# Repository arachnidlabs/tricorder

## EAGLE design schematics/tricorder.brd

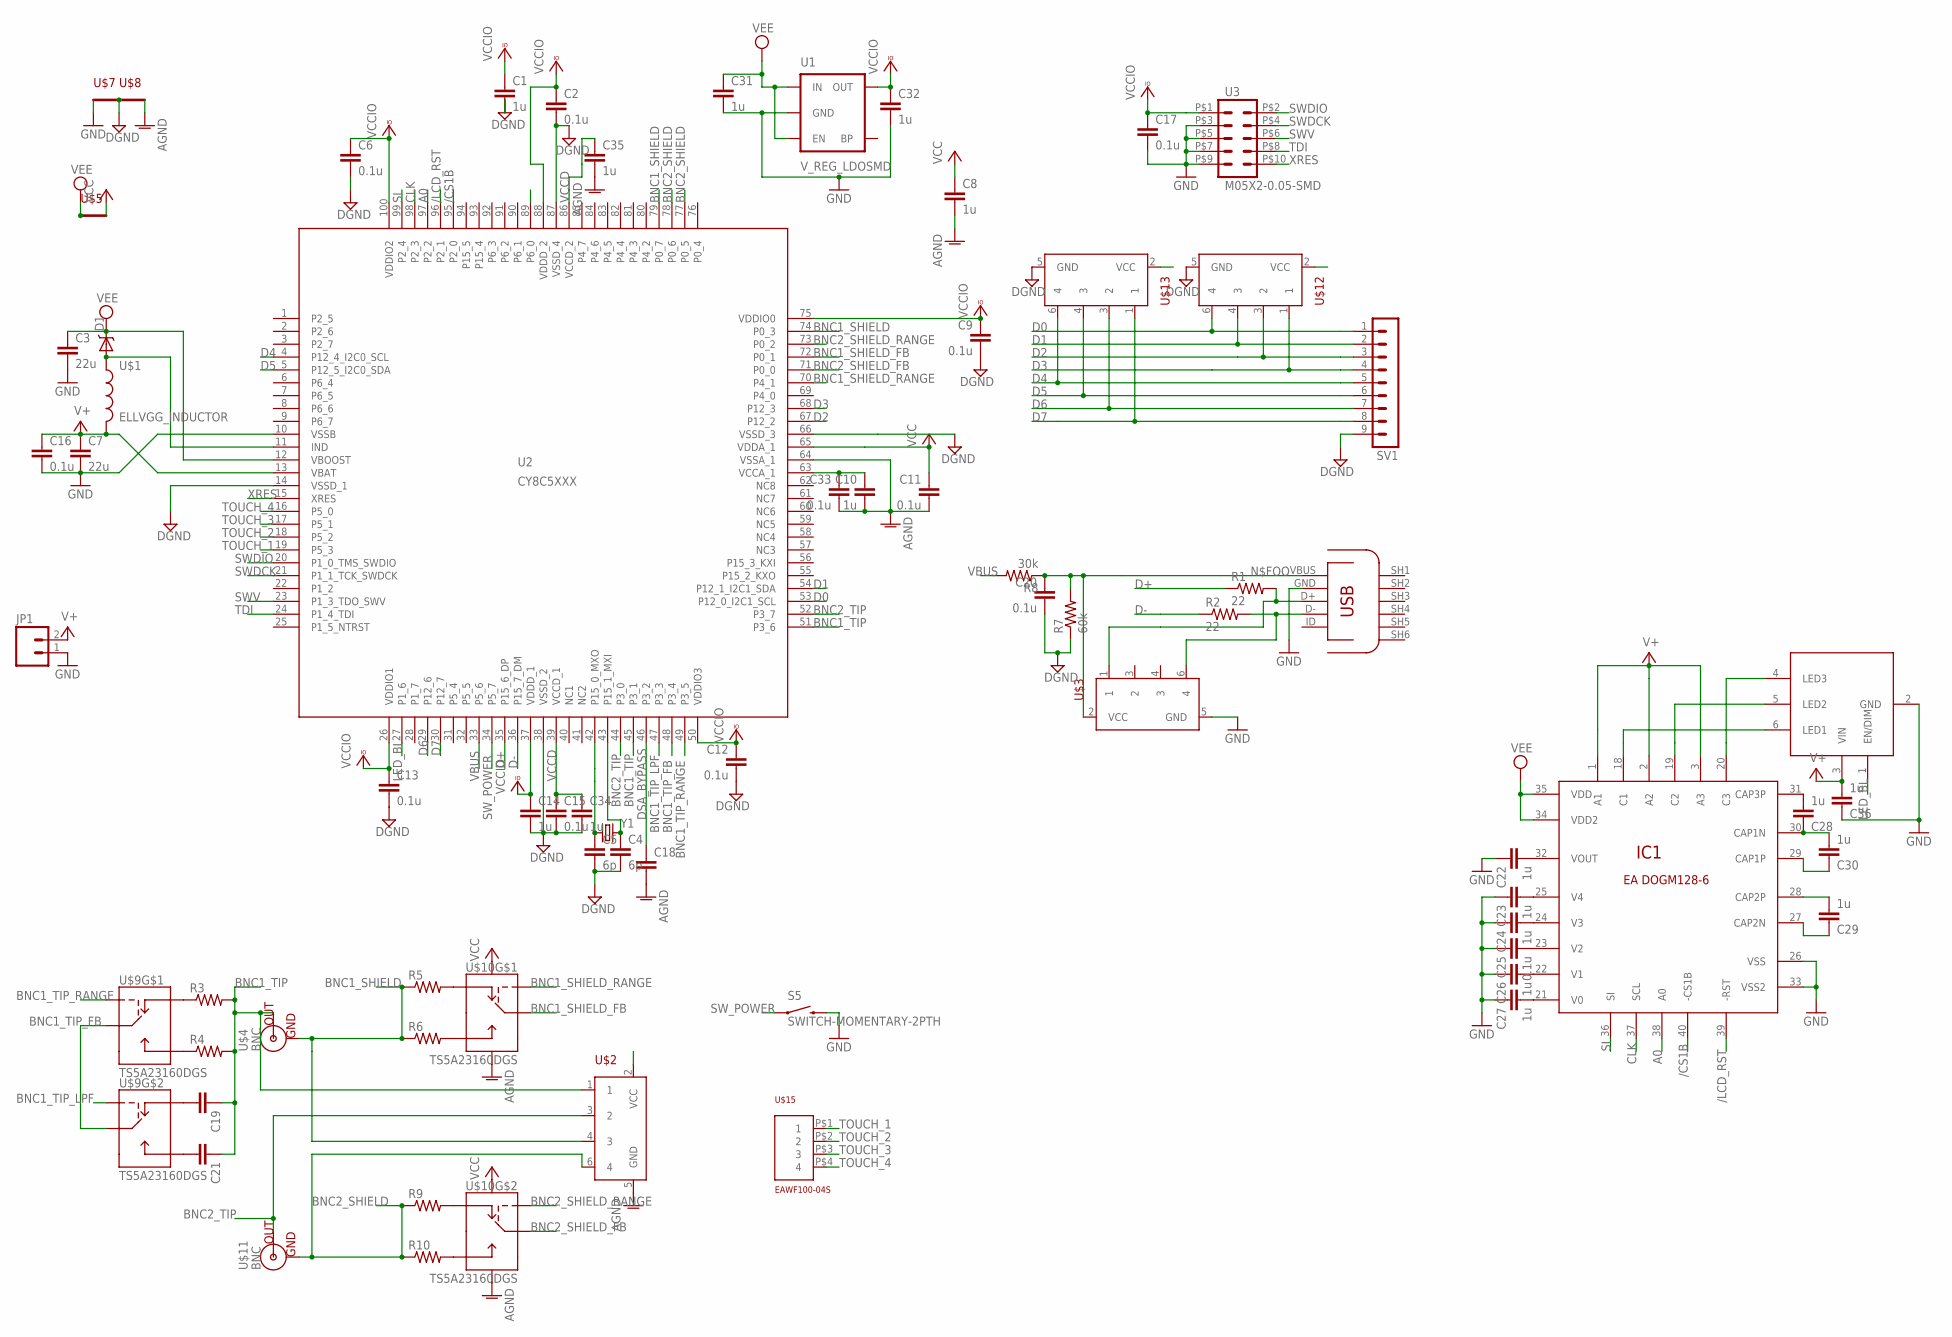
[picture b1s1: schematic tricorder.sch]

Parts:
C1, C8, C10, C14, C31, C32, C34, C35: 1u; 0603-CAP
C2, C9, C11, C15, C16, C20, C33: 0.1u; 0603-CAP
C3, C7: 22u; 0805
C4, C5: 6p; 0603-CAP
C6, C12, C13, C17, C25: 0.1u; C0603K
C18: CAP0805; 0805
C19, C21: CAP0603-CAP; 0603-CAP
C22, C23, C24, C26, C27, C28, C29, C30, C36: 1u; C0603K
D1: DIODE-SCHOTTKY_; SMA-DIODE
IC1: EADOGM128
JP1: M02PTH; 1X02
R1, R2: 22; 0603-RES
R3, R4, R5, R6, R9, R10: RESISTOR0603-RES; 0603-RES
R7: 60k; 0603-RES
R8: 30k; 0603-RES
S5: SWITCH-MOMENTARY-2PTH; TACTILE-PTH
SV1: MA09-1W
U1: V_REG_LDOSMD; SOT23-5
U2: CY8C5XXX; TQFP-14X14-100
U3: M05X2-0.05-SMD; PINHD-2X5-0.05-SMD
U7: MICROUSB; USB-MICROB
U$1: ELLVGG_INDUCTOR
U$2, U$3, U$12, U$13: ESD5V3U4RRSSOT363; SOT363_INFINEON
U$4, U$11: BNC; BNC_RA
U$5, U$7, U$8: SHORT-2
U$9, U$10: TS5A23160DGS; MSOP10
U$15: EAWF100-04S
U$16: CAT4003B; SOT23-6
Y1: XRCGB_XTAL; XRCGB-XTAL

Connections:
/CS1B: IC1.40 (-CS1B), U2.95 (P2_0)
/LCD_RST: IC1.39 (-RST), U2.96 (P2_1)
A0: IC1.38 (A0), U2.97 (P2_2)
AGND: C8.2, C10.2, C11.2, C18.2, C33.2, C35.2, U2.64 (VSSA_1), U$2.5 (GND), U$8.P$2, U$9.3 (GND), U$10.3 (GND)
BNC1_SHIELD: R5.1, R6.1, U2.74 (P0_3), U2.79 (P0_7), U$2.4 (3), U$4.SHIELD_1 (GND), U$4.SHIELD_2 (GND)
BNC1_SHIELD_FB: U2.72 (P0_1), U$10.10 (COM)
BNC1_SHIELD_RANGE: U2.70 (P4_1), U$10.1 (IN)
BNC1_TIP: C19.1, C21.1, R3.2, R4.2, U2.45 (P3_1), U2.51 (P3_6), U$2.1, U$4.TIP (OUT)
BNC1_TIP_FB: U2.48 (P3_4), U$9.6 (COM), U$9.10 (COM)
BNC1_TIP_LPF: U2.47 (P3_3), U$9.5 (IN)
BNC1_TIP_RANGE: U2.49 (P3_5), U$9.1 (IN)
BNC2_SHIELD: R9.1, R10.1, U2.77 (P0_5), U2.78 (P0_6), U$2.6 (4), U$11.SHIELD_1 (GND), U$11.SHIELD_2 (GND)
BNC2_SHIELD_FB: U2.71 (P0_0), U$10.6 (COM)
BNC2_SHIELD_RANGE: U2.73 (P0_2), U$10.5 (IN)
BNC2_TIP: U2.44 (P3_0), U2.52 (P3_7), U$2.3 (2), U$11.TIP (OUT)
CLK: IC1.37 (SCL), U2.98 (P2_3)
CLKI: C4.1, U2.43 (P15_1_MXI), Y1.2
CLKO: C5.1, U2.42 (P15_0_MXO), Y1.1
D0: SV1.1, U2.53 (P12_0_I2C1_SCL), U$12.6 (4)
D1: SV1.2, U2.54 (P12_1_I2C1_SDA), U$12.4 (3)
D2: SV1.3, U2.67 (P12_2), U$12.3 (2)
D3: SV1.4, U2.68 (P12_3), U$12.1
D4: SV1.5, U2.4 (P12_4_I2C0_SCL), U$13.6 (4)
D5: SV1.6, U2.5 (P12_5_I2C0_SDA), U$13.4 (3)
D6: SV1.7, U2.29 (P12_6), U$13.3 (2)
D7: SV1.8, U2.30 (P12_7), U$13.1
D+: R1.1, U2.35 (P15_6_DP)
D+IN: R1.2, U7.D+, U$3.1
D-: R2.1, U2.36 (P15_7_DM)
D-IN: R2.2, U7.D-, U$3.6 (4)
DGND: C1.2, C2.2, C4.2, C5.2, C6.2, C9.2, C12.2, C13.2, C14.2, C15.2, C20.2, C34.2, R7.1, SV1.9, U2.14 (VSSD_1), U2.38 (VSSD_2), U2.66 (VSSD_3), U2.87 (VSSD_4), U$7.P$2, U$8.P$1, U$12.5 (GND), U$13.5 (GND)
DSA_BYPASS: C18.1, U2.46 (P3_2)
GND: C3.2, C7.2, C16.2, C17.2, C22.1, C23.1, C24.1, C25.1, C26.1, C27.1, C31.2, C32.2, C36.1, IC1.26 (VSS), IC1.33 (VSS2), JP1.1, S5.3 (2), U1.2 (GND), U2.10 (VSSB), U3.P$3 (3), U3.P$5 (5), U3.P$7 (7), U3.P$9 (9), U7.GND, U$3.5 (GND), U$7.P$1, U$16.2 (GND)
LED_BL: U2.27 (P1_6), U$16.1 (EN/DIM)
unnamed: R3.1, U$9.9 (NC)
unnamed: R4.1, U$9.2 (NO)
unnamed: C10.1, C33.1, U2.63 (VCCA_1)
unnamed: R5.2, U$10.9 (NC)
unnamed: R6.2, U$10.2 (NO)
unnamed: C19.2, U$9.7 (NC)
unnamed: C21.2, U$9.4 (NO)
unnamed: R9.2, U$10.7 (NC)
unnamed: R10.2, U$10.4 (NO)
unnamed: C22.2, IC1.32 (VOUT)
unnamed: C23.2, IC1.25 (V4)
unnamed: C24.2, IC1.24 (V3)
unnamed: C25.2, IC1.23 (V2)
unnamed: C26.2, IC1.22 (V1)
unnamed: C27.2, IC1.21 (V0)
unnamed: C28.1, C30.2, IC1.30 (CAP1N)
unnamed: C28.2, IC1.31 (CAP3P)
unnamed: C30.1, IC1.29 (CAP1P)
unnamed: C29.2, IC1.28 (CAP2P)
unnamed: C29.1, IC1.27 (CAP2N)
unnamed: IC1.18 (C1), U$16.6 (LED1)
unnamed: IC1.19 (C2), U$16.5 (LED2)
unnamed: IC1.20 (C3), U$16.4 (LED3)
unnamed: D1.A, U2.11 (IND), U$1.P$1 (1)
N$FOO: C20.1, R7.2, R8.1, U7.VBUS (VCC), U$3.2 (VCC)
NC1: U$13.2 (VCC)
NC2: U$12.2 (VCC)
NC3: U$2.2 (VCC)
SI: IC1.36 (SI), U2.99 (P2_4)
SWDCK: U2.21 (P1_1_TCK_SWDCK), U3.P$4 (4)
SWDIO: U2.20 (P1_0_TMS_SWDIO), U3.P$2 (2)
SWV: U2.23 (P1_3_TDO_SWV), U3.P$6 (6)
SW_MENU: U2.89 (P6_0)
SW_POWER: S5.1, U2.34 (P5_7)
TDI: U2.24 (P1_4_TDI), U3.P$8 (8)
TOUCH_1: U2.19 (P5_3), U$15.P$1 (1)
TOUCH_2: U2.18 (P5_2), U$15.P$2 (2)
TOUCH_3: U2.17 (P5_1), U$15.P$3 (3)
TOUCH_4: U2.16 (P5_0), U$15.P$4 (4)
V+: C7.1, C16.1, C36.2, IC1.1 (A1), IC1.2 (A2), IC1.3 (A3), JP1.2, U2.13 (VBAT), U$1.P$2 (2), U$16.3 (VIN)
VBUS: R8.2, U2.33 (P5_6)
VCC: C8.1, C11.1, U2.65 (VDDA_1), U$5.P$2, U$9.8 (VCC), U$10.8 (VCC)
VCCD: C15.1, C34.1, C35.1, U2.39 (VCCD_1), U2.86 (VCCD_2)
VCCIO: C1.1, C2.1, C6.1, C9.1, C12.1, C13.1, C14.1, C17.1, C32.1, U1.5 (OUT), U2.26 (VDDIO1), U2.37 (VDDD_1), U2.50 (VDDIO3), U2.75 (VDDIO0), U2.88 (VDDD_2), U2.100 (VDDIO2), U3.P$1 (1)
VEE: C3.1, C31.1, D1.C, IC1.34 (VDD2), IC1.35 (VDD), U1.1 (IN), U1.3 (EN), U2.12 (VBOOST), U$5.P$1
XRES: U2.15 (XRES), U3.P$10 (10)

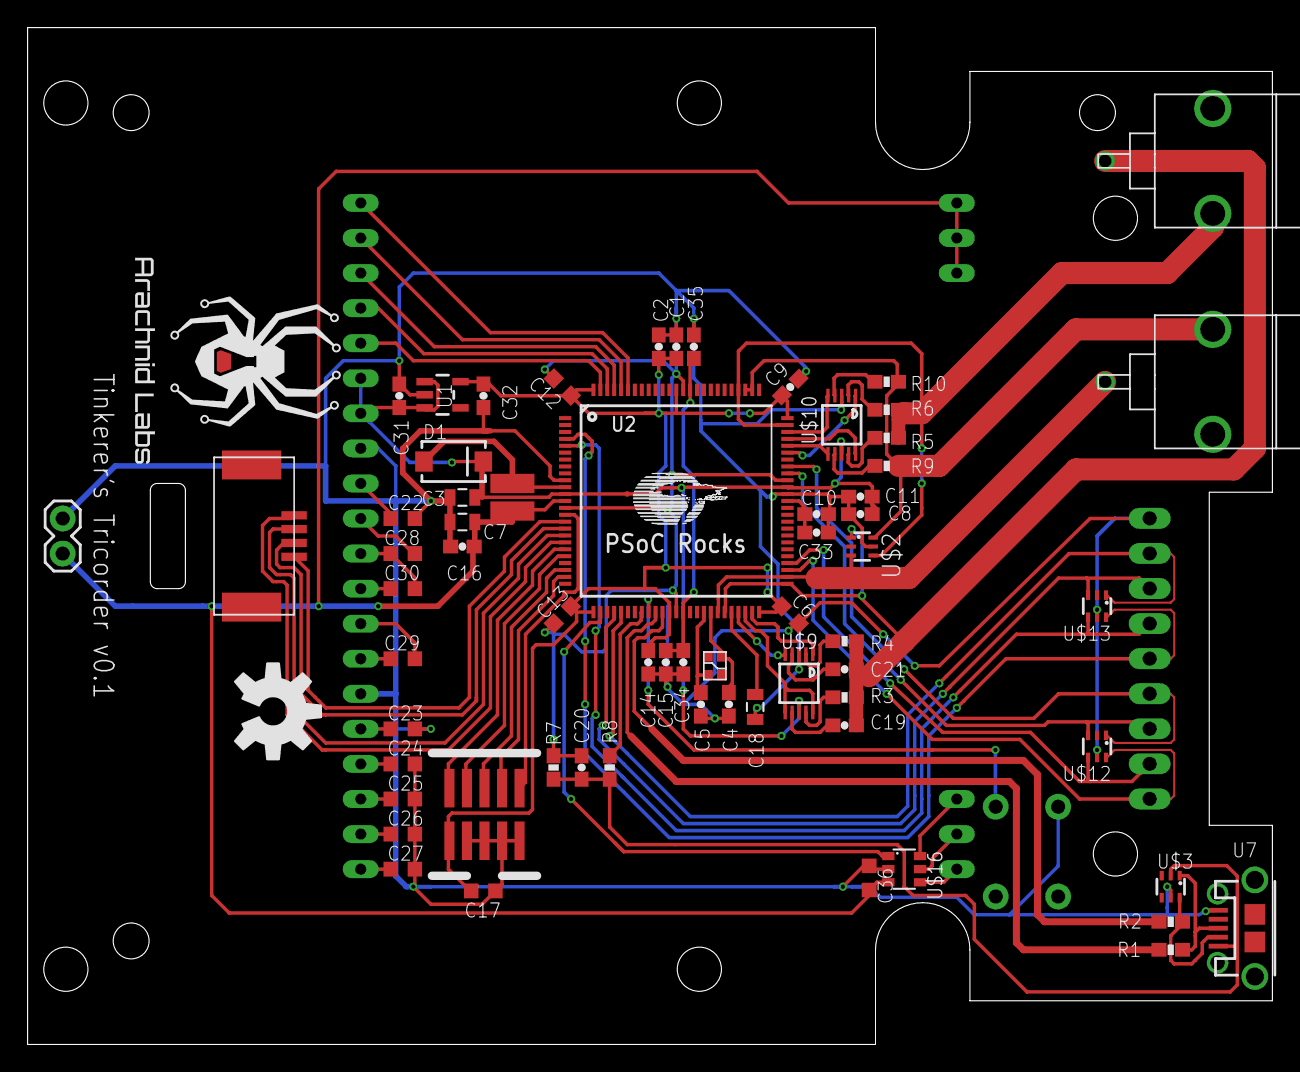
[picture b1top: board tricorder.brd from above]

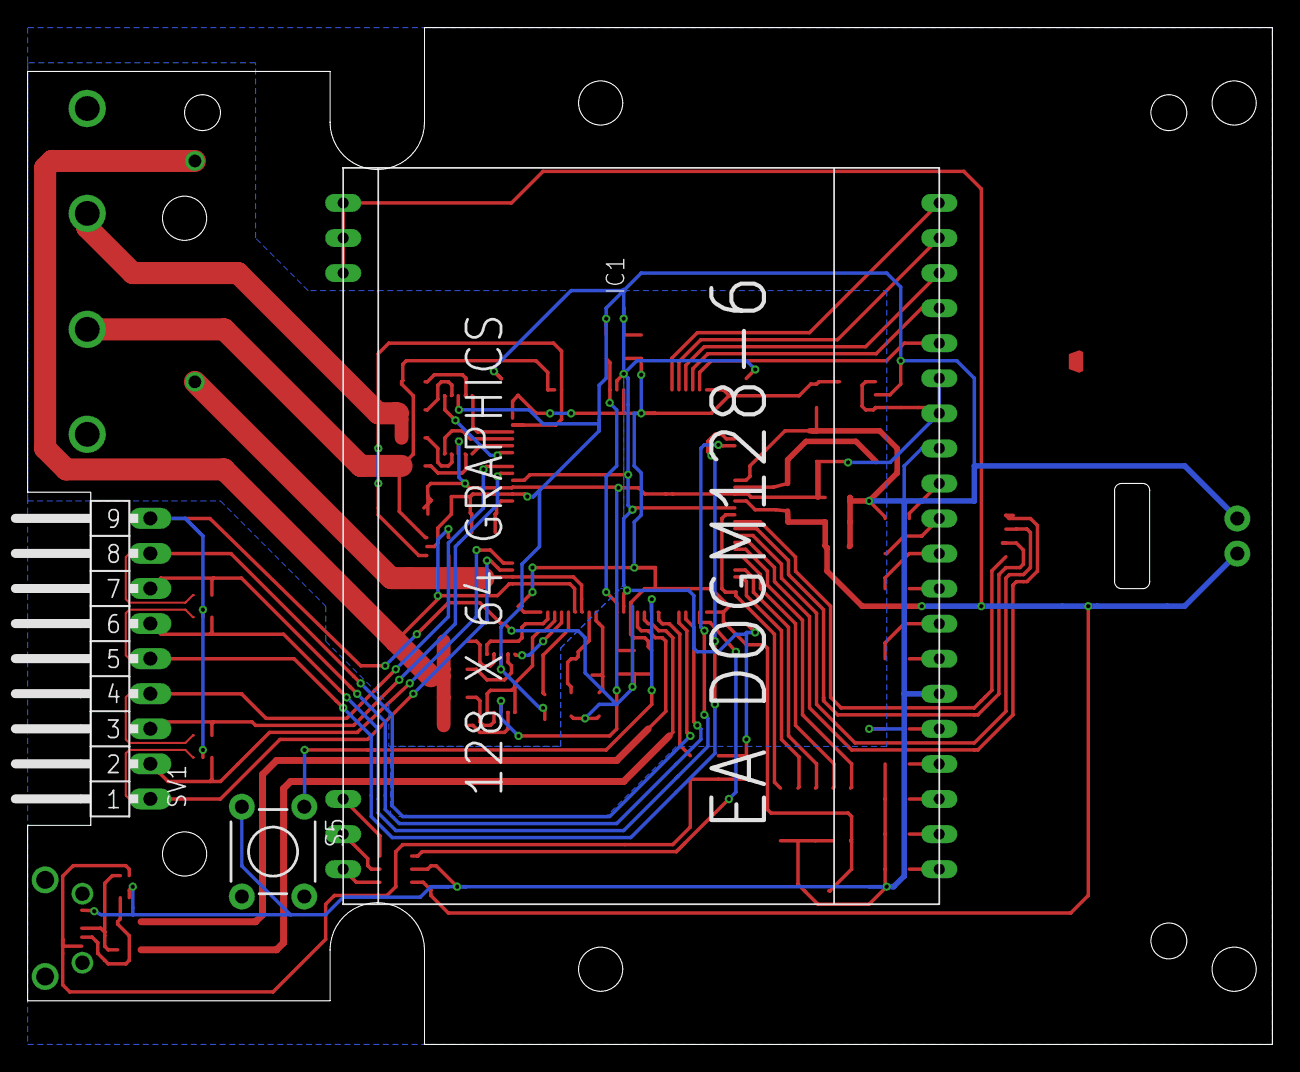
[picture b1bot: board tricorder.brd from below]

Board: 2 copper layers, 90.2 x 73.7 mm, 75 parts (5 on the bottom side), 76 nets.

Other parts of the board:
U$6: ARACHNID_LABS_LOGO
U$14: OSHW-LOGO-L
U$17, U$18, U$19: STENCIL8_FIDUCIAL

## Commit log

2013-05-21 Tweaked position of BNCs
2013-05-23 Design and layout modifications: onboard BNC, dedicated backlight controller
2013-05-27 Added submodule for freebooter
2013-05-27 Added TRM
2013-05-27 Initial version of tricorder code, forked from Phoenix impedance calculator
2013-06-02 Modified tricorder code so it compiles in a basic fashion; TRM and schematic fixes.
2013-06-09 Fixed LCD handling in firmware
2013-06-11 Tweaks to LCD display, enable boost regulator
2013-06-11 Remove generated_source from gitignore, since it contains some user modified files

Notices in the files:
parts and their libraries:
SparkFun-Passives: Licensing: CC v3.0 Share-Alike You are welcome to use this library for commercial purposes.
